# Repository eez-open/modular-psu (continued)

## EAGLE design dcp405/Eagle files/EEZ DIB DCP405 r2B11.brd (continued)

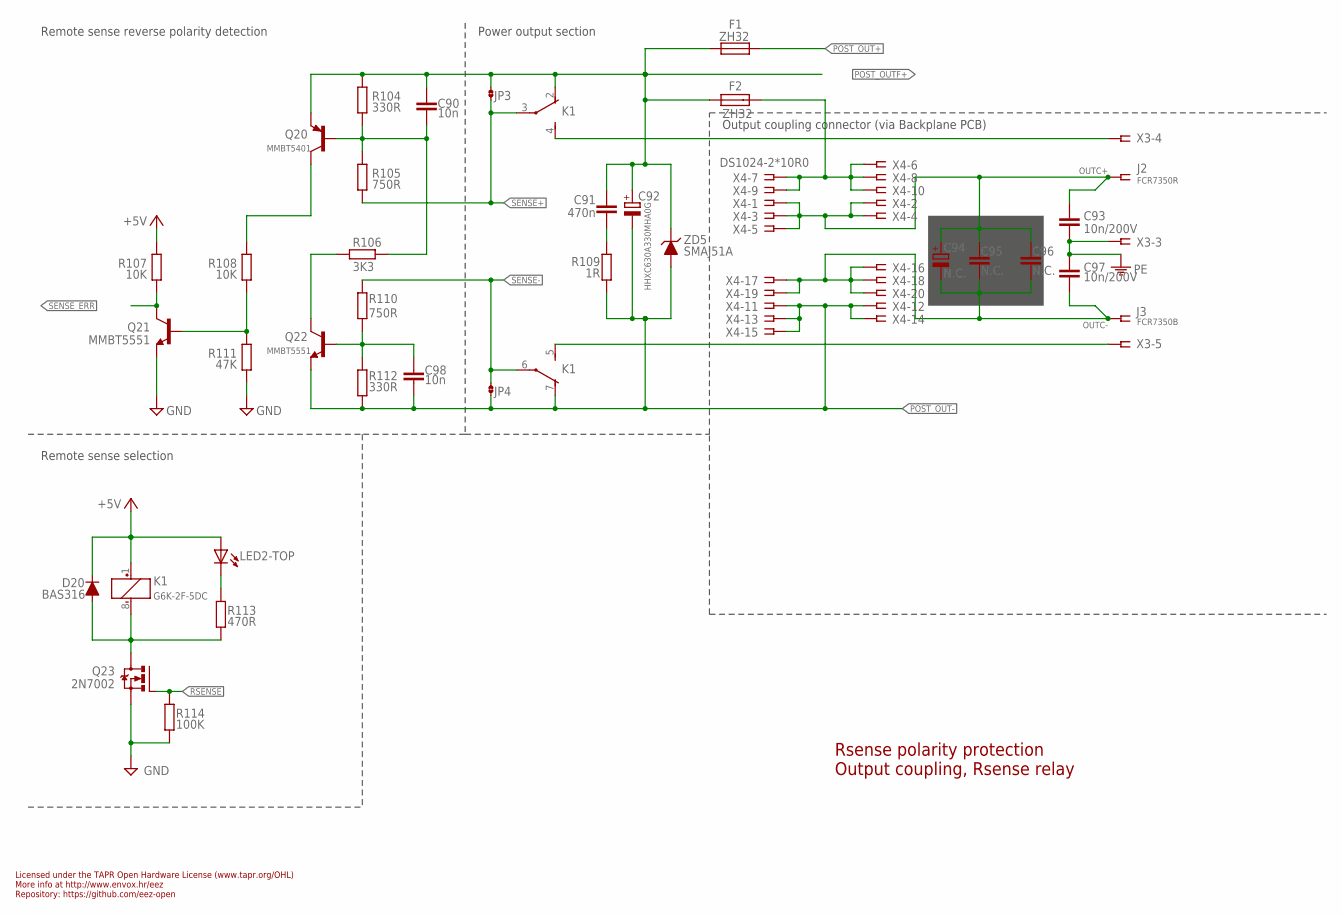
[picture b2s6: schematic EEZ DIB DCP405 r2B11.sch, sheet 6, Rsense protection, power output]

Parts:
C90, C98: 10n; C0805
C91: 470n; C0805
C92: HHXC630A330MHA0G; CAPAE830X1050N
C93, C97: 10n/200V; C1206
C94: N.C.; ECAP2/5
C95, C96: N.C.; C0805
D20: BAS316; SOD323-R
F1, F2: ZH32
J2: FCR7350R; S16N-PC
J3: FCR7350B; S16N-PC
JP3, JP4: JP2-CUT-0805; R_0805
K1: G6K-2F-5DC; G6K-2F; MPN G6K-2F DC24
LED2: WP934MD/2LID; WP934MD
Q20: MMBT5401; SOT23-BEC
Q21, Q22: MMBT5551; SOT23-BEC
Q23: 2N7002; SOT103P240X110-3N; MPN 2N7002-7-F
R104, R112: 330R; R0805
R105, R110: 750R; R0805
R106: 3K3; R0805
R107, R108: 10K; R0805
R109: 1R; R1206
R111: 47K; R0805
R113: 470R; R0805
R114: 100K; R0805
X3: 691322110005; MC1,5/5-G-3,5
X4: DS1024-2*10R0; SSW-110-02-T-D-RA
ZD5: SMAJ51A; DO214AA

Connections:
+5V: D20.C, K1.1 (+), LED2.TA (A), R107.2; also elsewhere on the board
GND: Q21.E, Q23.2 (S), R111.1, R114.1; also elsewhere on the board
unnamed: C90.2, Q20.B, R104.1, R105.2, R106.2
unnamed: Q20.C, R108.2
unnamed: Q22.C, R106.1
unnamed: C98.1, Q22.B, R110.1, R112.2
unnamed: Q21.B, R108.1, R111.2
unnamed: C91.2, R109.2
unnamed: D20.A, K1.8 (-), Q23.3 (D), R113.1
unnamed: K1.4 (S), X3.4
unnamed: K1.5 (S), X3.5
unnamed: LED2.TC (C), R113.2
OUTC+: C93.1, C94.+, C95.1, C96.1, J2.1, J2.NC1, J2.NC2, J2.NC3, J2.NC4, X4.1, X4.2, X4.3, X4.4, X4.5
OUTC-: C94.-, C95.2, C96.2, C97.2, J3.1, J3.NC1, J3.NC2, J3.NC3, J3.NC4, X4.16, X4.17, X4.18, X4.19, X4.20
OUTF+: F2.2, X4.6, X4.7, X4.8, X4.9, X4.10
PE: C93.2, C97.1, X3.3; also elsewhere on the board
POST_OUT+: F1.1; also elsewhere on the board
POST_OUT-: C92.-, C98.2, JP4.1, K1.7 (O), Q22.E, R109.1, R112.1, X4.11, X4.12, X4.13, X4.14, X4.15, ZD5.A; also elsewhere on the board
POST_OUTF+: C90.1, C91.1, C92.+, F1.2, F2.1, JP3.2, K1.2 (O), Q20.E, R104.2, ZD5.C; also elsewhere on the board
RSENSE: Q23.1 (G), R114.2; also elsewhere on the board
SENSE+: JP3.1, K1.3, R105.1; also elsewhere on the board
SENSE-: JP4.2, K1.6, R110.2; also elsewhere on the board
SENSE_ERR: Q21.C, R107.1; also elsewhere on the board

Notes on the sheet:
Rsense polarity protection Output coupling, Rsense relay
Licensed under the TAPR Open Hardware License (www.tapr.org/OHL)
Repository: https://github.com/eez-open
More info at http://www.envox.hr/eez
Remote sense reverse polarity detection
Remote sense selection
Output coupling connector (via Backplane PCB)
Power output section

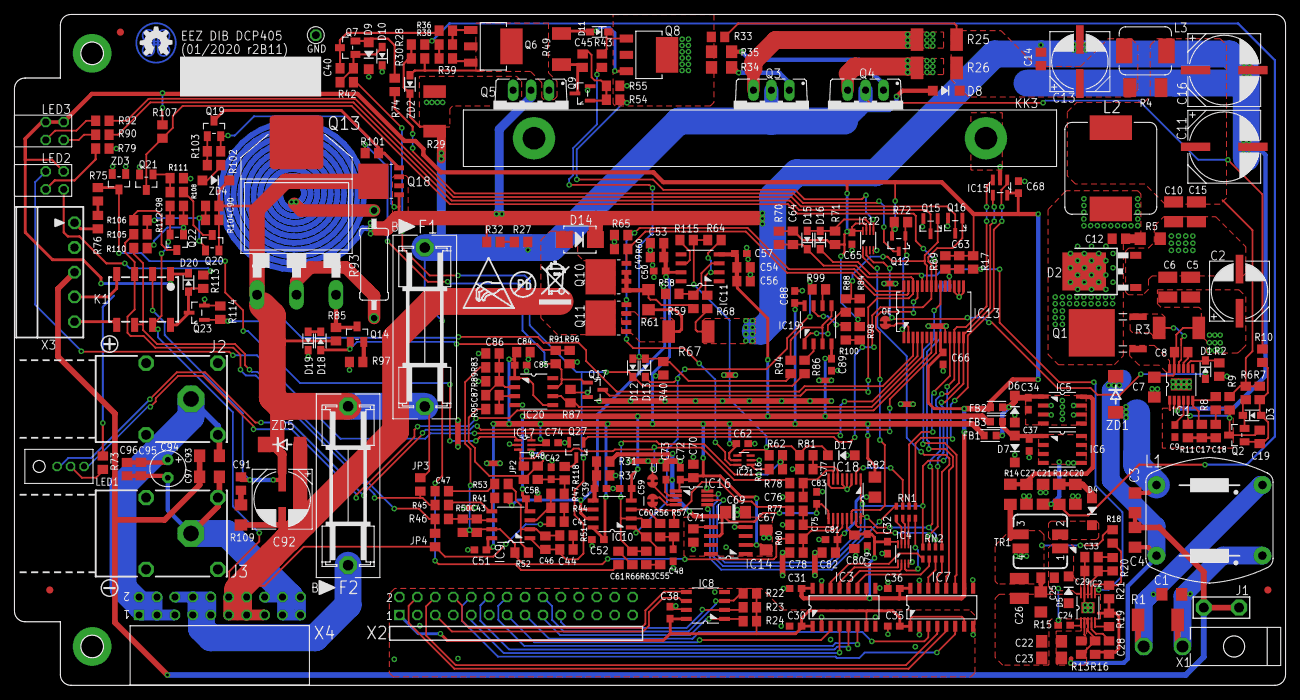
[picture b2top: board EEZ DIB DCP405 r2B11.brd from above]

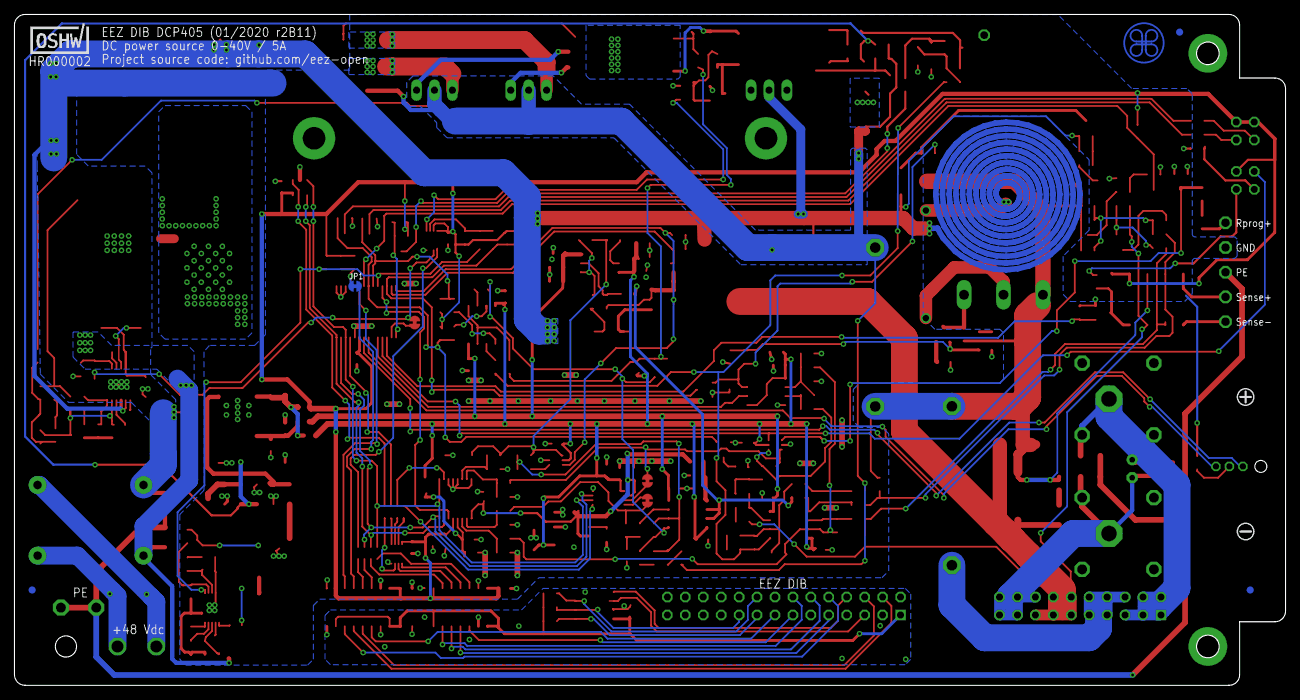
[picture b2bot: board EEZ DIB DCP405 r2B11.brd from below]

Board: 2 copper layers, 180.0 x 95.0 mm, 329 parts (2 on the bottom side), 197 nets.

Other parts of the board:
EEZ_SIGNATURE: SIGNATURESMALL; SIGNATURE_5MM
U$1: RECYCLE_BIN1/8
U$6: ESD_SYMBOL
U$7: PB_SMALL

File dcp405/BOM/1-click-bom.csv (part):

References,Qty,Description,Manufacturer,MPN,Digikey,Mouser,RS,Newark,Farnell
"C1, C3, C4, C93, C97",5,10n/200V,,311-4491-1-ND,311-4491-1-ND,603C1206KRX7RABB103,CC1206KRX7RABB103,,885342207005
"C10, C15",2,10u,,1276-6736-1-ND,1276-6736-1-ND,810C3216X7R1HK160AC,UMK316BBJ106KLT,,GRT31CR61H106KE01L
"C11, C16",1,EEEFK1J101P,,PCE3819CT-ND,PCE3819CT-ND,667EEEFK1J101P,EEEFK1J101P,,EEEFK1J101P
"C12, C19",2,470p,,732-7837-1-ND,732-7837-1-ND,710885012007038,0805CG471J9BB,,MC0805N471J500CT
C13,1,EEEFK1H470P,,PCE3815CT-ND,PCE3815CT-ND,667EEEFK1H470P,EEEFK1H470P,,EEEFK1H470P
"C17, C29, C46, C60",4,33p,,1276-1105-1-ND,1276-1105-1-ND,C0805C330K5GACTU,C0805C330J5GACTU,,MC0805N330J500CT
"C18, C55",2,6n8,,1276-1799-1-ND,1276-1799-1-ND,80C0805C682K5R,GRM2195C1H682JA01D,,MC0805B682K500CT
"C2, C92",2,HHXC630A330MHA0G,,-,-,661HHXC630A330MHA0G,,,
"C20, C21, C27, C67",4,4u7,,1276-2970-1-ND,1276-2970-1-ND,963EMK316B7475MLT,C1206C475K3RACTU,,C3216X7R1E475K160AC
"C22, C23",2,2u2,,1276-2723-1-ND,1276-2723-1-ND,80C1206C225M5RECLR,UMK316B7225KLHT,,
"C25, C63",2,330p,,1276-1189-1-ND,1276-1189-1-ND,80C0805C331J5G,0805N331J500CT,,C0805C331J5GACTU
C26,1,22u,,1276-3373-1-ND,1276-3373-1-ND,603CC121KKX7R8BB226,CL32A226KAJNNNE,,MC1210X226K250CT
"C28, C33, C49, C54",4,10n,,490-7194-1-ND,490-7194-1-ND,710885012207122,08055C103KAT2A,,VJ0805Y103JXXPW1BC
"C90, C98",2,10n,,490-7194-1-ND,490-7194-1-ND,710885012207122,08055C103KAT2A,,VJ0805Y103JXXPW1BC
"C41, C47",2,100p,,399-15000-1-ND,399-15000-1-ND,80C0805C101K5G,CC0805JRNP09BN101,,C0805C101JAGACTU
"C45, C53, C56, C70, C71, C80, C82",7,1u,,587-1283-1-ND,587-1283-1-ND,603CC805MKX7R7BB105,C0805C105K4RACTU,,VJ0805Y105KXXTW1BC
"C5, C6",2,4u7/100V,,587-5034-1-ND,587-5034-1-ND,810CGA6M3X7S2A475K,,,CGA6M3X7S2A475K200AB
"C61, C75, C76, C77, C78",5,4n7,,732-12255-1-ND,732-12255-1-ND,810C2012C0G1H472J1,C2012C0G1H472J060AA,,GRM2165C1H472JA01D
"C64, C86",2,1n,,732-7858-1-ND,732-7858-1-ND,710885012007040,GRM2195C1H102JA01D,,VJ0805A102JXACW1BC
C69,1,4u7 tant.,,399-9717-1-ND,399-9717-1-ND,80T491A475K006,T491A475K006AT,,T491A475K006AT
C7,1,1u/100V,,311-1948-6-ND,311-1948-6-ND,810C3216X7R2A105M,12061C105KAT2A,,C1206X105K1RACAUTO
"C8, C91",2,470n,,1276-6482-1-ND,1276-6482-1-ND,603CC805KKX7R9BB474,0805CG471J9BB,,MC0805F474Z500CT
C87,1,33n,,1276-1796-1-ND,1276-1796-1-ND,80C0805C333K5RAC,VJ0805Y333KXAAC,,MC0805B333K250CT
"C9, C24, C30, C31, C32, C34, C35, C36, C37, C38, C39, C42, C48, C50, C51, C52, C57, C58, C59, C65, C66, C68, C72, C73, C79, C81, C83, C88, C89",29,100n,,490-4774-1-ND,490-4774-1-ND,80C0603C104M4R,VJ0603Y104KXJAT,,C0603C104K4RAC7081
"C74,  C85",2,100n,,490-4774-1-ND,490-4774-1-ND,80C0603C104M4R,VJ0603Y104KXJAT,,C0603C104K4RAC7081
"D1, D3, D11, D12, D13, D16",6,BAS316,,1727-7370-1-ND,1727-7370-1-ND,771BAS316T/R,"BAS316,115",,"BAS316,115"
"D10, D15, D17, D18, D20",5,BAS316,,1727-7370-1-ND,1727-7370-1-ND,771BAS316T/R,"BAS316,115",,"BAS316,115"
D14,1,SK55,,SK55L-TPMSCT-ND,SK55L-TPMSCT-ND,833SK56ALTP,SK56B R4,,SK56C
D19,1,SK10100D1-DIO,,SBRT10U60D1-13DICT-ND,SBRT10U60D1-13DICT-ND,621SBRT10U60D1Q13,,,
D2,1,STPS15H100,,497-11400-5-ND,497-11400-5-ND,511STPS15H100CBTR,STPS15H100CBTR,,STPS15H100CBTR
"D4, D5",2,SKL16,,RB160MM-60CT-ND,RB160MM-60CT-ND,755RB160MM60TR,RB160MM60TR,,RB160MM60TR
"D6, D7",2,SKL14,,1727-7335-1-ND,1727-7335-1-ND,841PMEG4010EGWX,PMEG4010EGWX,,PMEG4010EGWX
D9,1,SKL14,,1727-7335-1-ND,1727-7335-1-ND,841PMEG4010EGWX,PMEG4010EGWX,,PMEG4010EGWX
"F1, F2",2,ZH32,,-,-,,,,
"FB1, FB2, FB3",3,BLM18AG102SH1D,,490-7809-1-ND,490-7809-1-ND,81BLM18AG102SH1D,BLM18AG102SH1D,,BLM18AG102SN1D
IC1,1,LTC3864EMSE#PBF,,LTC3864EMSE#PBF-ND,LTC3864EMSE#PBF-ND,584LTC3864EMSE#PBF,,,
IC10,1,MC33272ADR2G,,MC33272ADR2GOSCT-ND,MC33272ADR2GOSCT-ND,863MC33272ADR2G,MC33272ADR2G,,MC33272ADR2G
IC11,1,LTC2050HVCS8#PBF,,LTC2050HVCS8#PBF-ND,LTC2050HVCS8#PBF-ND,584LTC2050HVCS8#PBF,LTC2050HVCS8#PBF,,
IC12,1,74AUP1G74DC.125,,1727-6029-1-ND,1727-6029-1-ND,771AUP1GDC125,"74AUP1G74DC,125",,"74AUP1G74DC,125"
IC13,1,MCP23S17-E/SS,,MCP23S17-E/SS-ND,MCP23S17-E/SS-ND,579MCP23S17E/SS,MCP23S17E/SS,,MCP23S17E/SS
IC14,1,REF5025AIDR,,296-39165-1-ND,296-39165-1-ND,595REF5025AIDR,REF5025AID,,REF5025AIDG4
IC15,1,TC77-5.0MCTTR,,TC77-5.0MCTTRCT-ND,TC77-5.0MCTTRCT-ND,579TC775.0MCTTR,TC775.0MCTTR,,
IC16,1,DAC8552IDGKR,,296-46082-1-ND,296-46082-1-ND,595DAC8552IDGKR,,,
IC17,1,SN74LVC1G3157DCKR,,296-14909-1-ND,296-14909-1-ND,595SN74LVC1G3157DCK,SN74LVC1G3157DCKR,,SN74LVC1G3157DCKR
IC18,1,ADS1120IPWR,,296-37280-1-ND,296-37280-1-ND,595ADS1120IPWR,,,
IC19,1,LM293D,,296-12848-1-ND,296-12848-1-ND,511LM293DT,LM293ADR,,LM293DT
IC2,1,TPS54060DGQ,,296-37148-1-ND,296-37148-1-ND,595TPS54060DGQR,TPS54060DGQ,,TPS54060DGQ .
IC20,1,MAX9141ESA,,MAX9141ESA+-ND,MAX9141ESA+-ND,700MAX9141ESA,MAX9141ESA+,,MAX9141ESA+
"IC3, IC7",2,SI8641BB-B-IS1,,336-2566-ND,336-2566-ND,634SI8641BBBIS1,Si8641BBBIS1,,SI8641BBBIS1
IC4,1,SN74LVC1G139DCUR,,296-18203-1-ND,296-18203-1-ND,595SN74LVC1G139DCUR,,,SN74LVC1G139DCUR
IC5,1,MC78L05,,MC78L05ACDR2GOSCT-ND,MC78L05ACDR2GOSCT-ND,863MC78L05ACDR2G,MC78L05ACDG,,MC78L05ABDR2G
IC6,1,MC79L05,,MC79L05ABDGOS-ND,MC79L05ABDGOS-ND,863MC79L05ACDR2G,MC79L05ACDR2G,,MC79L05ACDR2G
IC8,1,M24C32-WMN6P,,497-8644-1-ND,497-8644-1-ND,511M24C32RMN6TP,M24C32WMN6P,,M24C32WMN6P
IC9,1,TL072D,,,,,,,
J1,1,4907,,36-4907-ND,36-4907-ND,5344907,,,
J2,1,FCR7350R or BSM-420-R,,-,-,,SWEB 8094 Au / RT,,FCR7350R
J3,1,FCR7350B or BSM-420-B,,-,-,,SWEB 8094 Au / SW,,FCR7350B
"JP2, JP3, JP4",3,0R,,RMCF0805ZT0R00CT-ND,RMCF0805ZT0R00CT-ND,603RC0805FR070RL,,,MCWR08X0000FTL
K1,1,G6K-2F-5DC,,Z128-ND,Z128-ND,653G6K2FDC5,G6K2FY 5DC,,G6K2F 5DC
L1,1,RN112-4-02-0M7,,817-2100-ND,817-2100-ND,631RN1124020M7,,,
L2,1,125CDMCCDS-330MC,,308-2568-1-ND,308-2568-1-ND,851125CDMCCDS330MC,,,7443551331
L3,1,VLS6045AF-3R3N,,445-180834-1-ND,445-180834-1-ND,810VLS6045AF3R3N,,,IHLP2020CZER3R3M11
LED1,1,WP934MD/2LID,,754-2000-ND,754-2000-ND,604WP934MD2LID,,,
LED2,1,WP42WUM/EGW,,754-1718-ND,754-1718-ND,604WP42WUM/EGW,,,
LED3,1,WP934MD/LYLID,,754-2008-ND,754-2008-ND,604WP934MDLYLID,,,
Q1,1,SUD19P06-60,,SUD19P06-60-GE3CT-ND,SUD19P06-60-GE3CT-ND,781SUD19P0660GE3,SUD19P0660GE3,,SUD19P0660GE3
"Q10, Q11",2,PSMN0R9-25YLC,,1727-5292-1-ND,1727-5292-1-ND,771PSMN0R925YLC115,"PSMN0R925YLC,115",,"PSMN0R925YLC,115"
Q12,1,BSS84P,,BSS84PH6433XTMA1CT-ND,BSS84PH6433XTMA1CT-ND,726BSS84PH6327XTSA2,,,BSS84PH6327XTSA2
Q13,1,BTA26-600,,497-2427-5-ND,497-2427-5-ND,511BTA26600B,BTA26600BRG,,BTA26600BRG
Q14,1,FMMT493TA,,FMMT493CT-ND,FMMT493CT-ND,522FMMT493TA,FMMT493TA,,FMMT493ATA
"Q15, Q16",2,2N7002,,T2N7002AKLMCT-ND,T2N7002AKLMCT-ND,757T2N7002AKLM,2N7002,,2N7002K7
"Q17, Q23",2,2N7002,,T2N7002AKLMCT-ND,T2N7002AKLMCT-ND,757T2N7002AKLM,2N7002,,2N7002K7
Q18,1,PSMN013-60YL,,1727-2589-1-ND,1727-2589-1-ND,771PSMN01360YLX,,,PSMN01360YLX
"Q19, Q21, Q22",3,MMBT5551,,MMBT5551LT1GOSCT-ND,MMBT5551LT1GOSCT-ND,863MMBT5551LT1G,MMBT5551LT1G,,MMBT5551LT1G
Q2,1,MMBT5401,,MMBT5401-FDICT-ND,MMBT5401-FDICT-ND,621MMBT5401F,MMBT5401,,MMBT5401LT3G
"Q7, Q20",2,MMBT5401,,MMBT5401-FDICT-ND,MMBT5401-FDICT-ND,621MMBT5401F,MMBT5401,,MMBT5401LT3G
"Q3, Q4",2,D45H11FP,,497-2578-5-ND,497-2578-5-ND,863D45H11G,D45H11G,,D45H11G
Q5,1,FQPF11P06,,FQPF11P06FS-ND,FQPF11P06FS-ND,512FQPF11P06,FQPF11P06,,
Q6,1,BCP56,,BCP5616QTADICT-ND,BCP5616QTADICT-ND,621BCP5616QTA,BCP5616T3G,,BCP56TX
Q8,1,NZT605,,NZT605CT-ND,NZT605CT-ND,512NZT605,NZT605,,NZT605
Q9,1,BSS205NH6327XTSA1,,BSS205NH6327XTSA1CT-ND,BSS205NH6327XTSA1CT-ND,BSS205NH6327XTSA1,BSS205NH6327XTSA1,,BSS205NH6327XTSA1
"R104, R110",2,750R,,A126385CT-ND,A126385CT-ND,71CRCW0805750RFKEB,RN73C2A750RB,,MCWR08X7500FTL
"R109, R61",2,1R,,311-1.00CRCT-ND,311-1.00CRCT-ND,603RC0805FR131RL,CR0805J/1R0ELF,,MCWR08W1R00FTL
"R11, R27, R32, R54, R84, R87, R97, R99",8,4K7,,311-4.70KCRCT-ND,311-4.70KCRCT-ND,603RC0805FR074K7L,CRG0805F4K7,,CRGCQ0805F4K7
"R30, R36, R70",3,4K7,,311-4.70KCRCT-ND,311-4.70KCRCT-ND,603RC0805FR074K7L,CRG0805F4K7,,CRGCQ0805F4K7
"R13, R60, R65",3,47K,,RHM47KKCT-ND,RHM47KKCT-ND,603RC0805FR0747KL,CRCW080547K0FKEA,,MCWR08X4702FTL
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
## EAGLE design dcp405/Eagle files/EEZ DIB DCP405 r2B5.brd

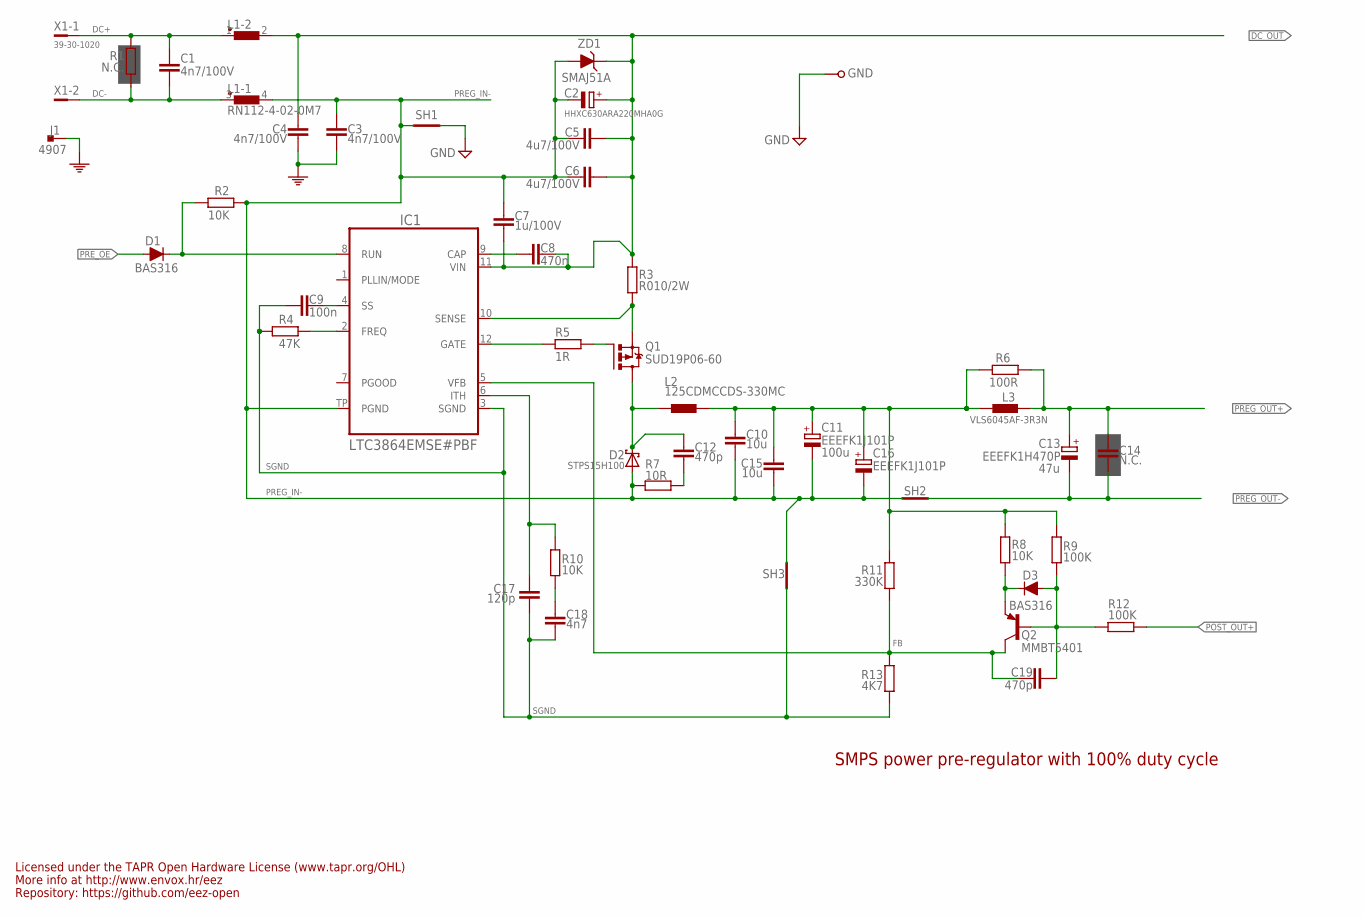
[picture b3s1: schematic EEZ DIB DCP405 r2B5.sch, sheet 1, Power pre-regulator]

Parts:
C1, C3, C4: 4n7/100V; C1206
C2: HHXC630ARA220MHA0G; CAPAE830X1050N
C5, C6: 4u7/100V; C1210
C7: 1u/100V; C1206
C8: 470n; C0805
C9: 100n; C0603
C10, C15: 10u; C1210
C11, C16: EEEFK1J101P; CAPAE1030X1050N
C12, C19: 470p; C0805
C13: EEEFK1H470P; CAPAE830X1050N
C14: N.C.; C0805
C17: 120p; C0805
C18: 4n7; C0805
D1, D3: BAS316; SOD323-R
D2: STPS15H100; TO252-L
GND: PCB_TEST_TABSHIELD; PCB_SHIELD_TAB
IC1: LTC3864EMSE#PBF; LTC_05-08-1666
J1: 4907; PCB_TAB-4907
L1: RN112-4-02-0M7; RN112
L2: 125CDMCCDS-330MC; 125CDMCC/DS
L3: VLS6045AF-3R3N; COILCRAFT_HPI0630
Q1: SUD19P06-60; TO229P990X239-3N
Q2: MMBT5401; SOT23-BEC
R1: N.C.; R2512
R2, R8, R10: 10K; R0805
R3: R010/2W; R2512
R4: 47K; R0805
R5: 1R; R0805
R6: 100R; R0805
R7: 10R; R1206
R9, R12: 100K; R0805
R11: 330K; R0805
R13: 4K7; R0805
SH1: SHORTNOHOLE; SHORT_NOHOLE
SH2: Pgnd to Pout- short; SHORT_NOHOLE
SH3: Sgnd to Pgnd short; SHORT_NOHOLE
X1: 39-30-1020; MINIFIT_39301020
ZD1: SMAJ51A; DO214AA

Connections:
DC+: C1.2, L1.1, R1.2, X1.1
DC-: C1.1, L1.3 (1), R1.1, X1.2
DC_OUT: C2.+, C4.2, C5.1, C6.1, C7.1, C8.2, IC1.11 (VIN), L1.2, R3.1, ZD1.C; also elsewhere on the board
FB: C19.1, IC1.5 (VFB), Q2.C, R11.2, R13.1
GND: GND.1, SH1.2 (GND_B); also elsewhere on the board
L_OUT: C10.1, C11.+, C15.1, C16.+, L2.2, L3.1, R6.1, R8.1, R9.1, R11.1
unnamed: D3.C, Q2.E, R8.2
unnamed: C18.1, R10.1
unnamed: D1.C, IC1.8 (RUN), R2.2
unnamed: C17.1, IC1.6 (ITH), R10.2
unnamed: C8.1, IC1.9 (CAP)
unnamed: IC1.2 (FREQ), R4.1
unnamed: C9.2, IC1.4 (SS)
unnamed: Q1.1 (G), R5.2
unnamed: IC1.12 (GATE), R5.1
unnamed: C12.2, R7.2
unnamed: C19.2, D3.A, Q2.B, R9.2, R12.1
PE: C3.2, C4.1, J1.1, J1.2; also elsewhere on the board
POST_OUT+: R12.2; also elsewhere on the board
PREG_IN-: C2.-, C3.1, C5.2, C6.2, C7.2, C10.2, C11.-, C15.2, C16.-, D2.1 (A), D2.2 (A), IC1.TP (PGND), L1.4 (2), R2.1, R7.1, SH1.1 (GND_A), SH2.2 (GND_B), SH3.2 (GND_B), ZD1.A
PREG_OUT+: C13.+, C14.1, L3.2, R6.2; also elsewhere on the board
PREG_OUT-: C13.-, C14.2, SH2.1 (GND_A); also elsewhere on the board
PRE_OE: D1.A; also elsewhere on the board
SENSE: IC1.10 (SENSE), Q1.3 (S), R3.2
SGND: C9.1, C17.2, C18.2, IC1.3 (SGND), R4.2, R13.2, SH3.1 (GND_A)
SW: C12.1, D2.3 (C), L2.1, Q1.2 (D)

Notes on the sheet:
47u
Licensed under the TAPR Open Hardware License (www.tapr.org/OHL)
Repository: https://github.com/eez-open
More info at http://www.envox.hr/eez
SMPS power pre-regulator with 100% duty cycle
100u

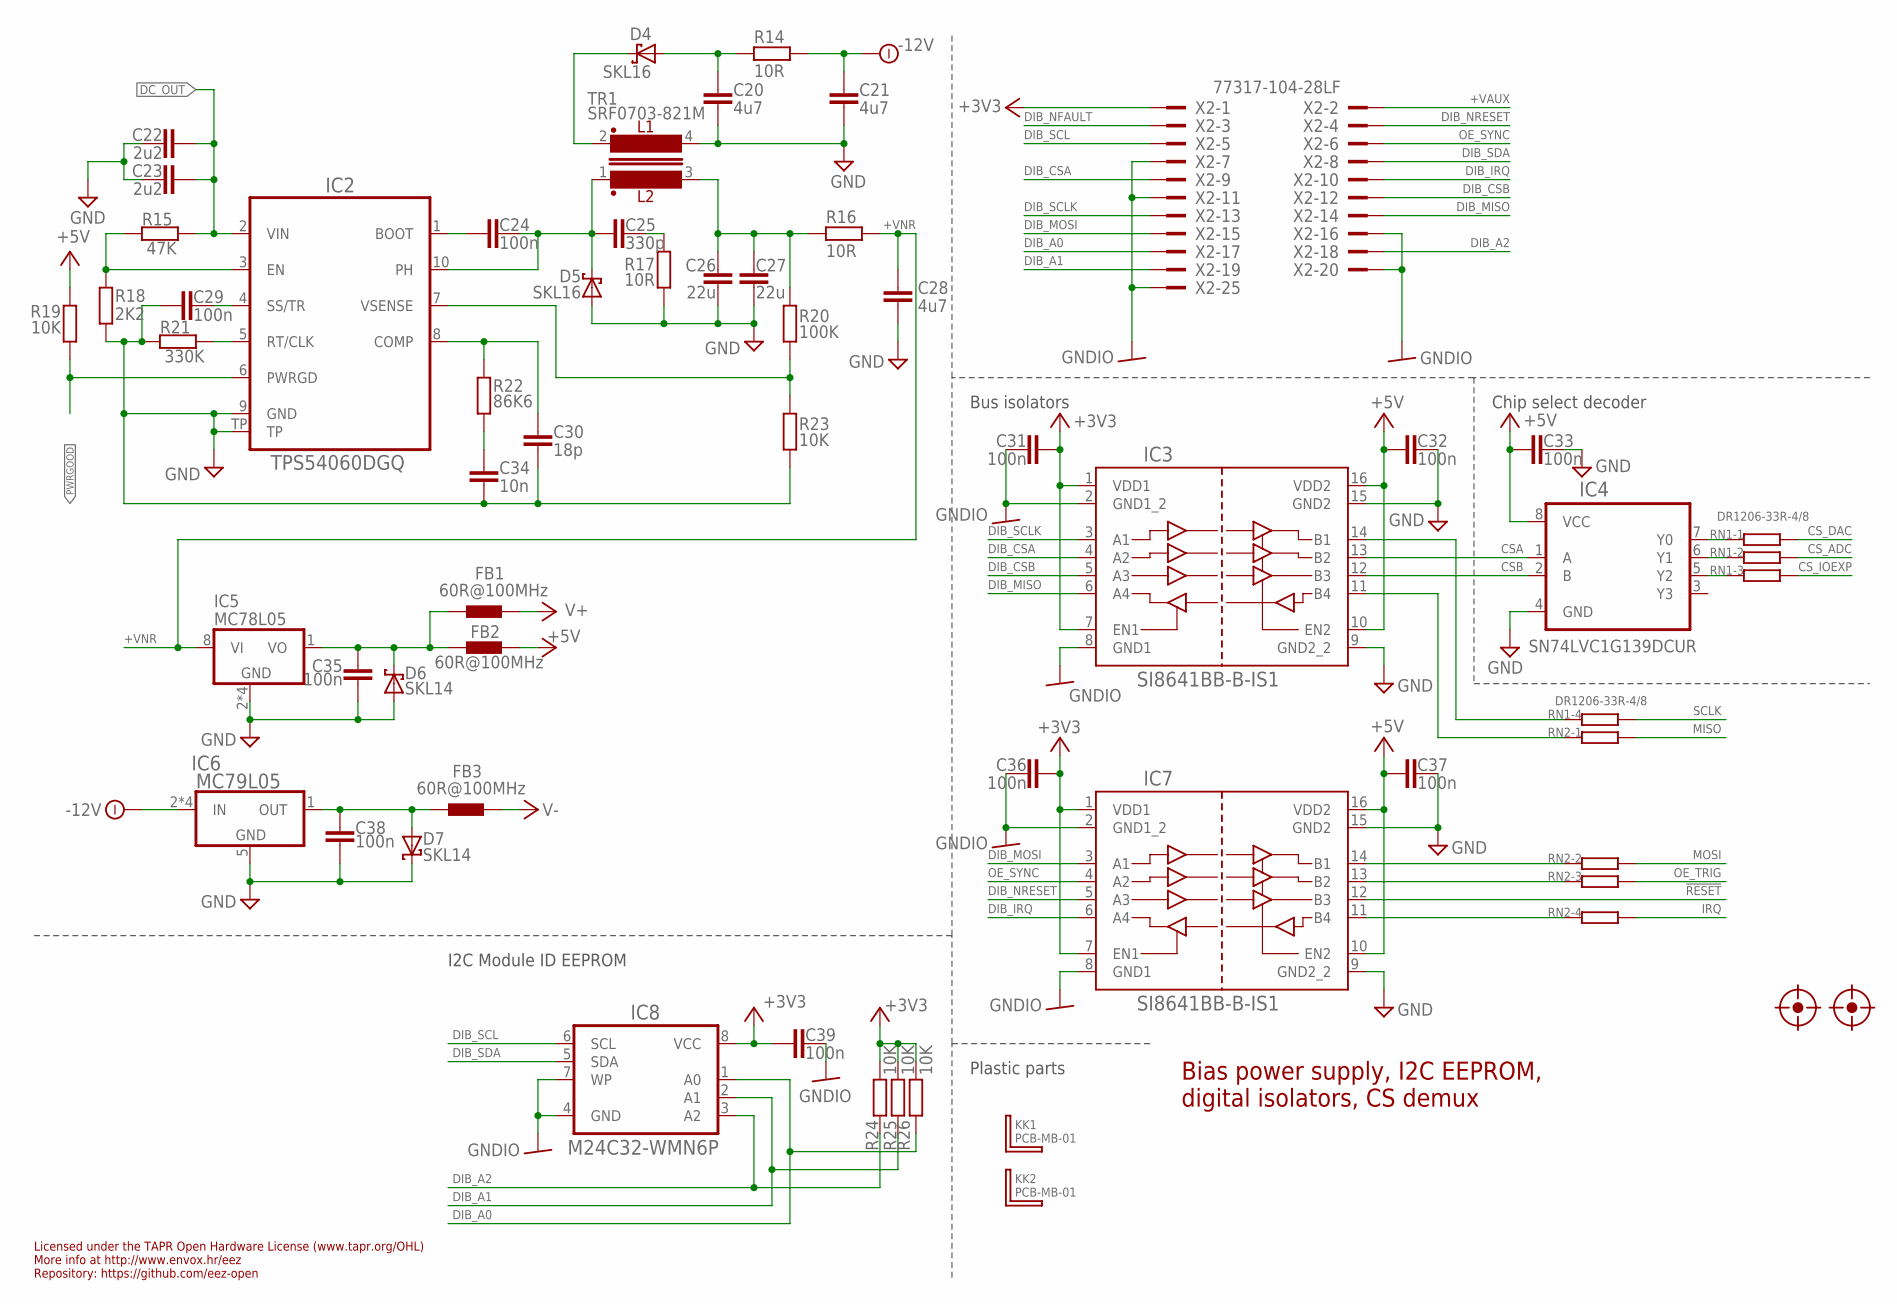
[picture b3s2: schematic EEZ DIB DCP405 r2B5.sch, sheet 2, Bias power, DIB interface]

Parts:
C20, C21, C28: 4u7; C1206
C22, C23: 2u2; C1206
C24, C29, C31, C32, C33, C35, C36, C37, C38, C39: 100n; C0603
C25: 330p; C0805
C26, C27: 22u; C1206
C30: 18p; C0603
C34: 10n; C0805
D4, D5: SKL16; SOD123
D6, D7: SKL14; SOD123
FB1, FB2, FB3: 60R@100MHz; BEAD0603
FM1, FM2: FIDUCIAL_2; FIDUCIAL_DUAL
IC2: TPS54060DGQ; SOP50P490X110-11N
IC3, IC7: SI8641BB-B-IS1; SOIC-16
IC4: SN74LVC1G139DCUR; DCU8
IC5: MC78L05; SOIC127P600X173-8N
IC6: MC79L05; SOIC127P600X173-8N
IC8: M24C32-WMN6P; SOIC127P600X173-8N
KK1, KK2: PCB-MB-01; PCB-MB
R14, R16, R17: 10R; R1206
R15: 47K; R0805
R18: 2K2; R0805
R19, R23, R24, R25, R26: 10K; R0805
R20: 100K; R0805
R21: 330K; R0805
R22: 86K6; R0805
RN1, RN2: DR1206-33R-4/8; CAY16
TR1: SRF0703-821M; SRF0703
X2: 77317-104-28LF

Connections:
!RESET: IC7.12 (B3); also elsewhere on the board
+3V3: C31.1, C36.1, C39.2, IC3.1 (VDD1), IC3.7 (EN1), IC7.1 (VDD1), IC7.7 (EN1), IC8.8 (VCC), R24.1, R25.1, R26.1, X2.1
+5V: C32.2, C33.1, C37.2, FB2.P$2 (2), IC3.10 (EN2), IC3.16 (VDD2), IC4.8 (VCC), IC7.10 (EN2), IC7.16 (VDD2), R19.1; also elsewhere on the board
+5VOUT: C35.1, D6.C, FB1.P$1 (1), FB2.P$1 (1), IC5.1 (VO)
+VAUX: X2.2
+VNR: C28.1, IC5.8 (VI), R16.1
-12V: C21.1, IC6.2 (IN), IC6.3 (IN), IC6.6 (IN), IC6.7 (IN), R14.1; also elsewhere on the board
CSA: IC3.13 (B2), IC4.1 (A)
CSB: IC3.12 (B3), IC4.2 (B)
CS_ADC: RN1.7 (2); also elsewhere on the board
CS_DAC: RN1.8 (2); also elsewhere on the board
CS_IOEXP: RN1.6 (2); also elsewhere on the board
DC_OUT: C22.1, C23.1, IC2.2 (VIN), R15.2; also elsewhere on the board
DIB_A0: IC8.1 (A0), R26.2, X2.17
DIB_A1: IC8.2 (A1), R25.2, X2.19
DIB_A2: IC8.3 (A2), R24.2, X2.18
DIB_CSA: IC3.4 (A2), X2.9
DIB_CSB: IC3.5 (A3), X2.12
DIB_IRQ: IC7.6 (A4), X2.10
DIB_MISO: IC3.6 (A4), X2.14
DIB_MOSI: IC7.3 (A1), X2.15
DIB_NFAULT: X2.3
DIB_NRESET: IC7.5 (A3), X2.4
DIB_SCL: IC8.6 (SCL), X2.5
DIB_SCLK: IC3.3 (A1), X2.13
DIB_SDA: IC8.5 (SDA), X2.8
GND: C20.2, C21.2, C22.2, C23.2, C26.2, C27.2, C28.2, C29.2, C30.1, C32.1, C33.2, C34.1, C35.2, C37.1, C38.1, D5.A, D6.A, D7.C, IC2.9 (GND), IC2.TP, IC3.9 (GND2_2), IC3.15 (GND2), IC4.4 (GND), IC5.2 (GND), IC5.3 (GND), IC5.6 (GND), IC5.7 (GND), IC6.5 (GND), IC7.9 (GND2_2), IC7.15 (GND2), R17.1, R18.1, R21.1, R23.1, TR1.4; also elsewhere on the board
GNDIO: C31.2, C36.2, C39.1, IC3.2 (GND1_2), IC3.8 (GND1), IC7.2 (GND1_2), IC7.8 (GND1), IC8.4 (GND), IC8.7 (WP), X2.7, X2.11, X2.16, X2.20, X2.25
IRQ: RN2.5 (2); also elsewhere on the board
MISO: RN2.8 (2); also elsewhere on the board
MOSI: RN2.7 (2); also elsewhere on the board
unnamed: IC7.13 (B2), RN2.3 (1)
unnamed: IC4.5 (Y2), RN1.3 (1)
unnamed: IC4.7 (Y0), RN1.1
unnamed: IC3.11 (B4), RN2.1
unnamed: IC7.11 (B4), RN2.4 (1)
unnamed: IC4.6 (Y1), RN1.2 (1)
unnamed: C25.2, R17.2
unnamed: C38.2, D7.A, FB3.P$1 (1), IC6.1 (OUT)
unnamed: IC2.3 (EN), R15.1, R18.2
unnamed: C29.1, IC2.4 (SS/TR)
unnamed: IC2.5 (RT/CLK), R21.2
unnamed: C30.2, IC2.8 (COMP), R22.2
unnamed: C34.2, R22.1
unnamed: C24.2, IC2.1 (BOOT)
unnamed: IC7.14 (B1), RN2.2 (1)
unnamed: IC2.7 (VSENSE), R20.1, R23.2
unnamed: IC3.14 (B1), RN1.4 (1)
unnamed: C20.1, D4.A, R14.2
OE_SYNC: IC7.4 (A2), X2.6
OE_TRIG: RN2.6 (2); also elsewhere on the board
PH: C24.1, C25.1, D5.C, IC2.10 (PH), TR1.1
PWRGOOD: IC2.6 (PWRGD), R19.2; also elsewhere on the board
SCLK: RN1.5 (2); also elsewhere on the board
V+: FB1.P$2 (2); also elsewhere on the board
V-: FB3.P$2 (2); also elsewhere on the board
VOUT+: C26.1, C27.1, R16.2, R20.2, TR1.3
VOUT-: D4.C, TR1.2

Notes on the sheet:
Licensed under the TAPR Open Hardware License (www.tapr.org/OHL)
Repository: https://github.com/eez-open
More info at http://www.envox.hr/eez
I2C Module ID EEPROM
Bus isolators
Bias power supply, I2C EEPROM, digital isolators, CS demux
Plastic parts
Chip select decoder

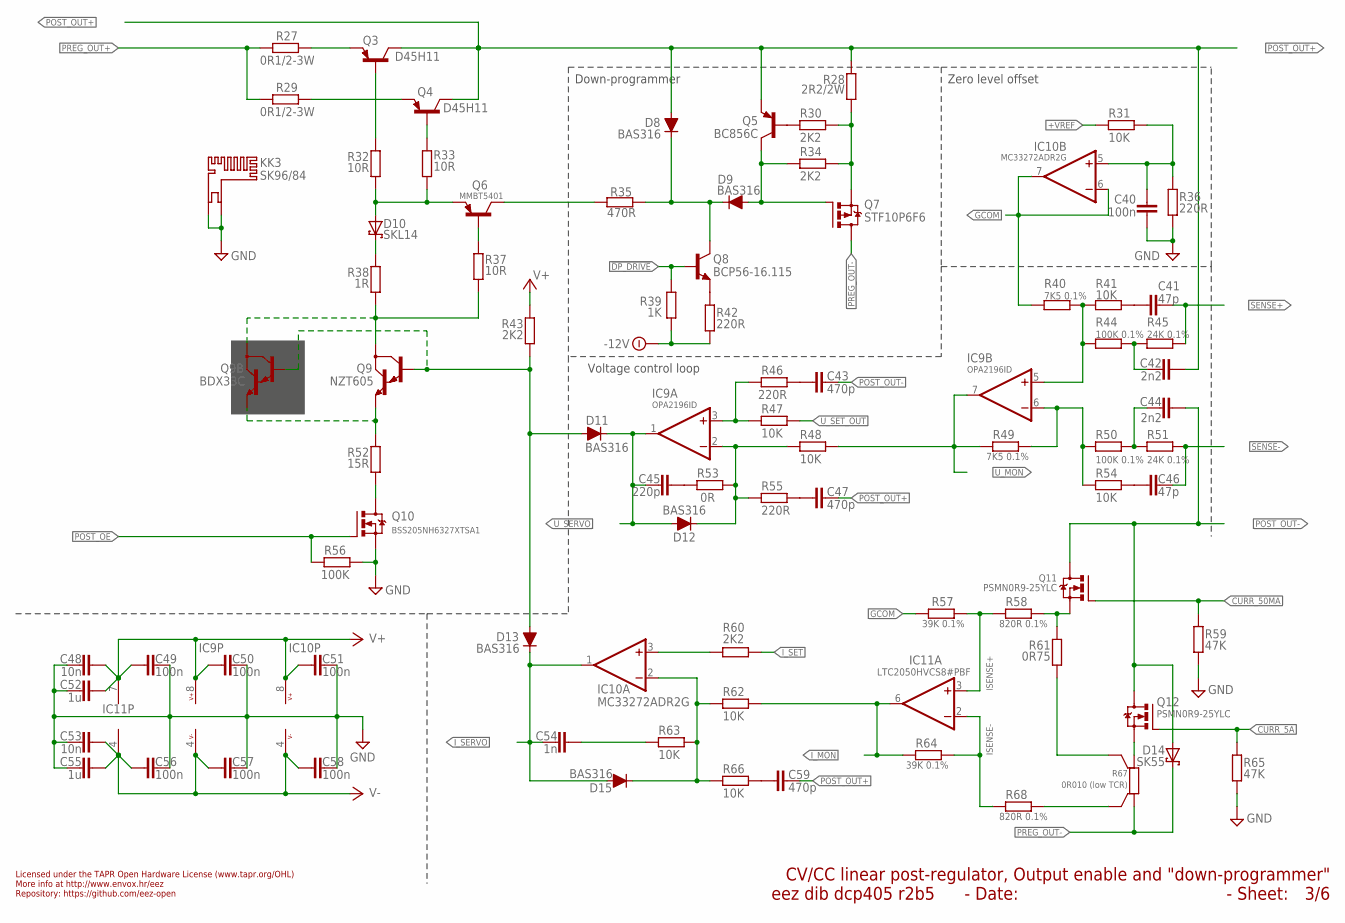
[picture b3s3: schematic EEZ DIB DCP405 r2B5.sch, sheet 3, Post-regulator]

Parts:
C40, C49, C50, C51, C56, C57, C58: 100n; C0603
C41, C46: 47p; C0805
C42, C44: 2n2; C0805
C43, C47, C59: 470p; C0805
C45: 220p; C0805
C48, C53: 10n; C0805
C52, C55: 1u; C0805
C54: 1n; C0805
D8, D9, D11, D12, D13, D15: BAS316; SOD323-R
D10: SKL14; SOD123
D14: SK55; SMB
IC9: OPA2196ID; SOIC127P600X173-8N
IC10: MC33272ADR2G; SOIC127P600X173-8N
IC11: LTC2050HVCS8#PBF; SOIC127P600X173-8N
KK3: SK96/84
Q3, Q4: D45H11; TO220BV
Q5: BC856C; SOT23-BEC
Q6: MMBT5401; SOT23-BEC
Q7: STF10P6F6; TO220BV
Q8: BCP56-16.115; SOT230P700X180-4N
Q9: NZT605; SOT230P700X180-4N
Q9B: BDX33C; TO220BV
Q10: BSS205NH6327XTSA1; SOT103P240X110-3N; MPN 2N7002-7-F
Q11, Q12: PSMN0R9-25YLC; SOT669
R27, R29: 0R1/2-3W; R2512
R28: 2R2/2W; R2512
R30, R34, R43, R60: 2K2; R0805
R31, R41, R47, R48, R54, R62, R63, R66: 10K; R0805
R32, R33, R37: 10R; R1206
R35: 470R; R0805
R36, R42, R46, R55: 220R; R0805
R38: 1R; R0805
R39: 1K; R0805
R40, R49: 7K5 0.1%; R0805
R44, R50: 100K 0.1%; R0805
R45, R51: 24K 0.1%; R0805
R52: 15R; R1206
R53: 0R; R0805
R56: 100K; R0805
R57, R64: 39K 0.1%; R0805
R58, R68: 820R 0.1%; R0805
R59, R65: 47K; R0805
R61: 0R75; R1206
R67: 0R010 (low TCR); R_2512-4WIRE

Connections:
5A_S: Q12.1 (S), Q12.2 (S), Q12.3 (S), R67.2
50MA_S: Q11.1 (S), Q11.2 (S), Q11.3 (S), R58.1, R61.1
!DP_DRIVE: Q8.1 (B), R39.1; also elsewhere on the board
+VREF: R31.1; also elsewhere on the board
-12V: R39.2, R42.2; also elsewhere on the board
CURR_5A: Q12.4 (G), R65.2; also elsewhere on the board
CURR_50MA: Q11.4 (G), R59.2; also elsewhere on the board
DARL_C: Q9.2 (C), Q9.4 (C), Q9B.2 (C), R37.1, R38.1
DP_S: Q7.3 (S), R28.1, R30.1, R34.1
GCOM: IC10.6 (-IN), IC10.7 (OUT), R40.1, R57.1
GND: C40.2, C48.1, C49.2, C50.1, C51.1, C52.1, C53.1, C55.1, C56.2, C57.1, C58.1, KK3.1, KK3.2, Q10.2 (S), R36.2, R56.1, R59.1, R65.1; also elsewhere on the board
ISENSE+: IC11.3 (+IN), R57.2, R58.2
ISENSE-: IC11.2 (-IN), R64.1, R68.2
I_MON: IC11.6 (OUT), R62.1, R64.2; also elsewhere on the board
I_SERVO: C54.2, D13.C, D15.A, IC10.1 (OUT); also elsewhere on the board
I_SET: R60.1; also elsewhere on the board
LOOP_CTRL: D11.A, D13.A, Q9.1 (B), Q9B.1 (B), R43.1
unnamed: R61.2, R67.2S
unnamed: C45.1, R53.2
unnamed: Q10.3 (D), R52.1
unnamed: C54.1, R63.1
unnamed: Q6.B, R37.2
unnamed: Q4.1 (B), R33.2
unnamed: Q4.3 (E), R29.2
unnamed: Q3.1 (B), R32.2
unnamed: D10.A, Q6.E, R32.1, R33.1
unnamed: Q6.C, R35.2
unnamed: Q9.3 (E), Q9B.3 (E), R52.2
unnamed: D10.C, R38.2
unnamed: Q3.3 (E), R27.2
unnamed: IC10.3 (+IN), R60.2
unnamed: IC9.3 (+IN), R46.2, R47.2
unnamed: D12.C, IC9.2 (-IN), R48.2, R53.1, R55.2
unnamed: C44.1, R50.2, R51.1
unnamed: C41.2, R41.1
unnamed: C46.2, R54.1
unnamed: C59.2, R66.1
unnamed: D15.C, IC10.2 (-IN), R62.2, R63.2, R66.2
unnamed: C43.2, R46.1
unnamed: C47.2, R55.1
unnamed: Q8.3 (E), R42.1
unnamed: Q5.B, R30.2
unnamed: C40.1, IC10.5 (+IN), R31.2, R36.1
unnamed: C42.1, R44.2, R45.1
unnamed: D9.A, Q5.C, Q7.1 (G), R34.2
unnamed: IC9.5 (+IN), R40.2, R41.2, R44.1
unnamed: IC9.6 (-IN), R49.2, R50.1, R54.2
unnamed: R67.1S, R68.1
POST_OE: Q10.1 (G), R56.2; also elsewhere on the board
POST_OUT+: C42.2, C47.1, C59.1, D8.A, Q3.2 (C), Q4.2 (C), Q5.E, R28.2; also elsewhere on the board
POST_OUT-: C43.1, C44.2, D14.A, Q11.MB (D), Q12.MB (D); also elsewhere on the board
PREG_OUT+: R27.1, R29.1; also elsewhere on the board
PREG_OUT-: D14.C, Q7.2 (D), R67.1; also elsewhere on the board
Q6C: D8.C, D9.C, Q8.2 (C), Q8.4 (C), R35.1
SENSE+: C41.1, R45.2; also elsewhere on the board
SENSE-: C46.1, R51.2; also elsewhere on the board
U_MON: IC9.7 (OUT), R48.1, R49.1; also elsewhere on the board
U_SERVO: C45.2, D11.C, D12.A, IC9.1 (OUT); also elsewhere on the board
U_SET_OUT: R47.1; also elsewhere on the board
V+: C48.2, C49.1, C50.2, C51.2, C52.2, IC9.8 (V+), IC10.8 (V+), IC11.7 (V+), R43.2; also elsewhere on the board
V-: C53.2, C55.2, C56.1, C57.2, C58.2, IC9.4 (V-), IC10.4 (V-), IC11.4 (V-); also elsewhere on the board

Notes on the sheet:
Voltage control loop
Down-programmer
Licensed under the TAPR Open Hardware License (www.tapr.org/OHL)
Repository: https://github.com/eez-open
More info at http://www.envox.hr/eez
Zero level offset
CV/CC linear post-regulator, Output enable and "down-programmer"
- Sheet:
- Date:
